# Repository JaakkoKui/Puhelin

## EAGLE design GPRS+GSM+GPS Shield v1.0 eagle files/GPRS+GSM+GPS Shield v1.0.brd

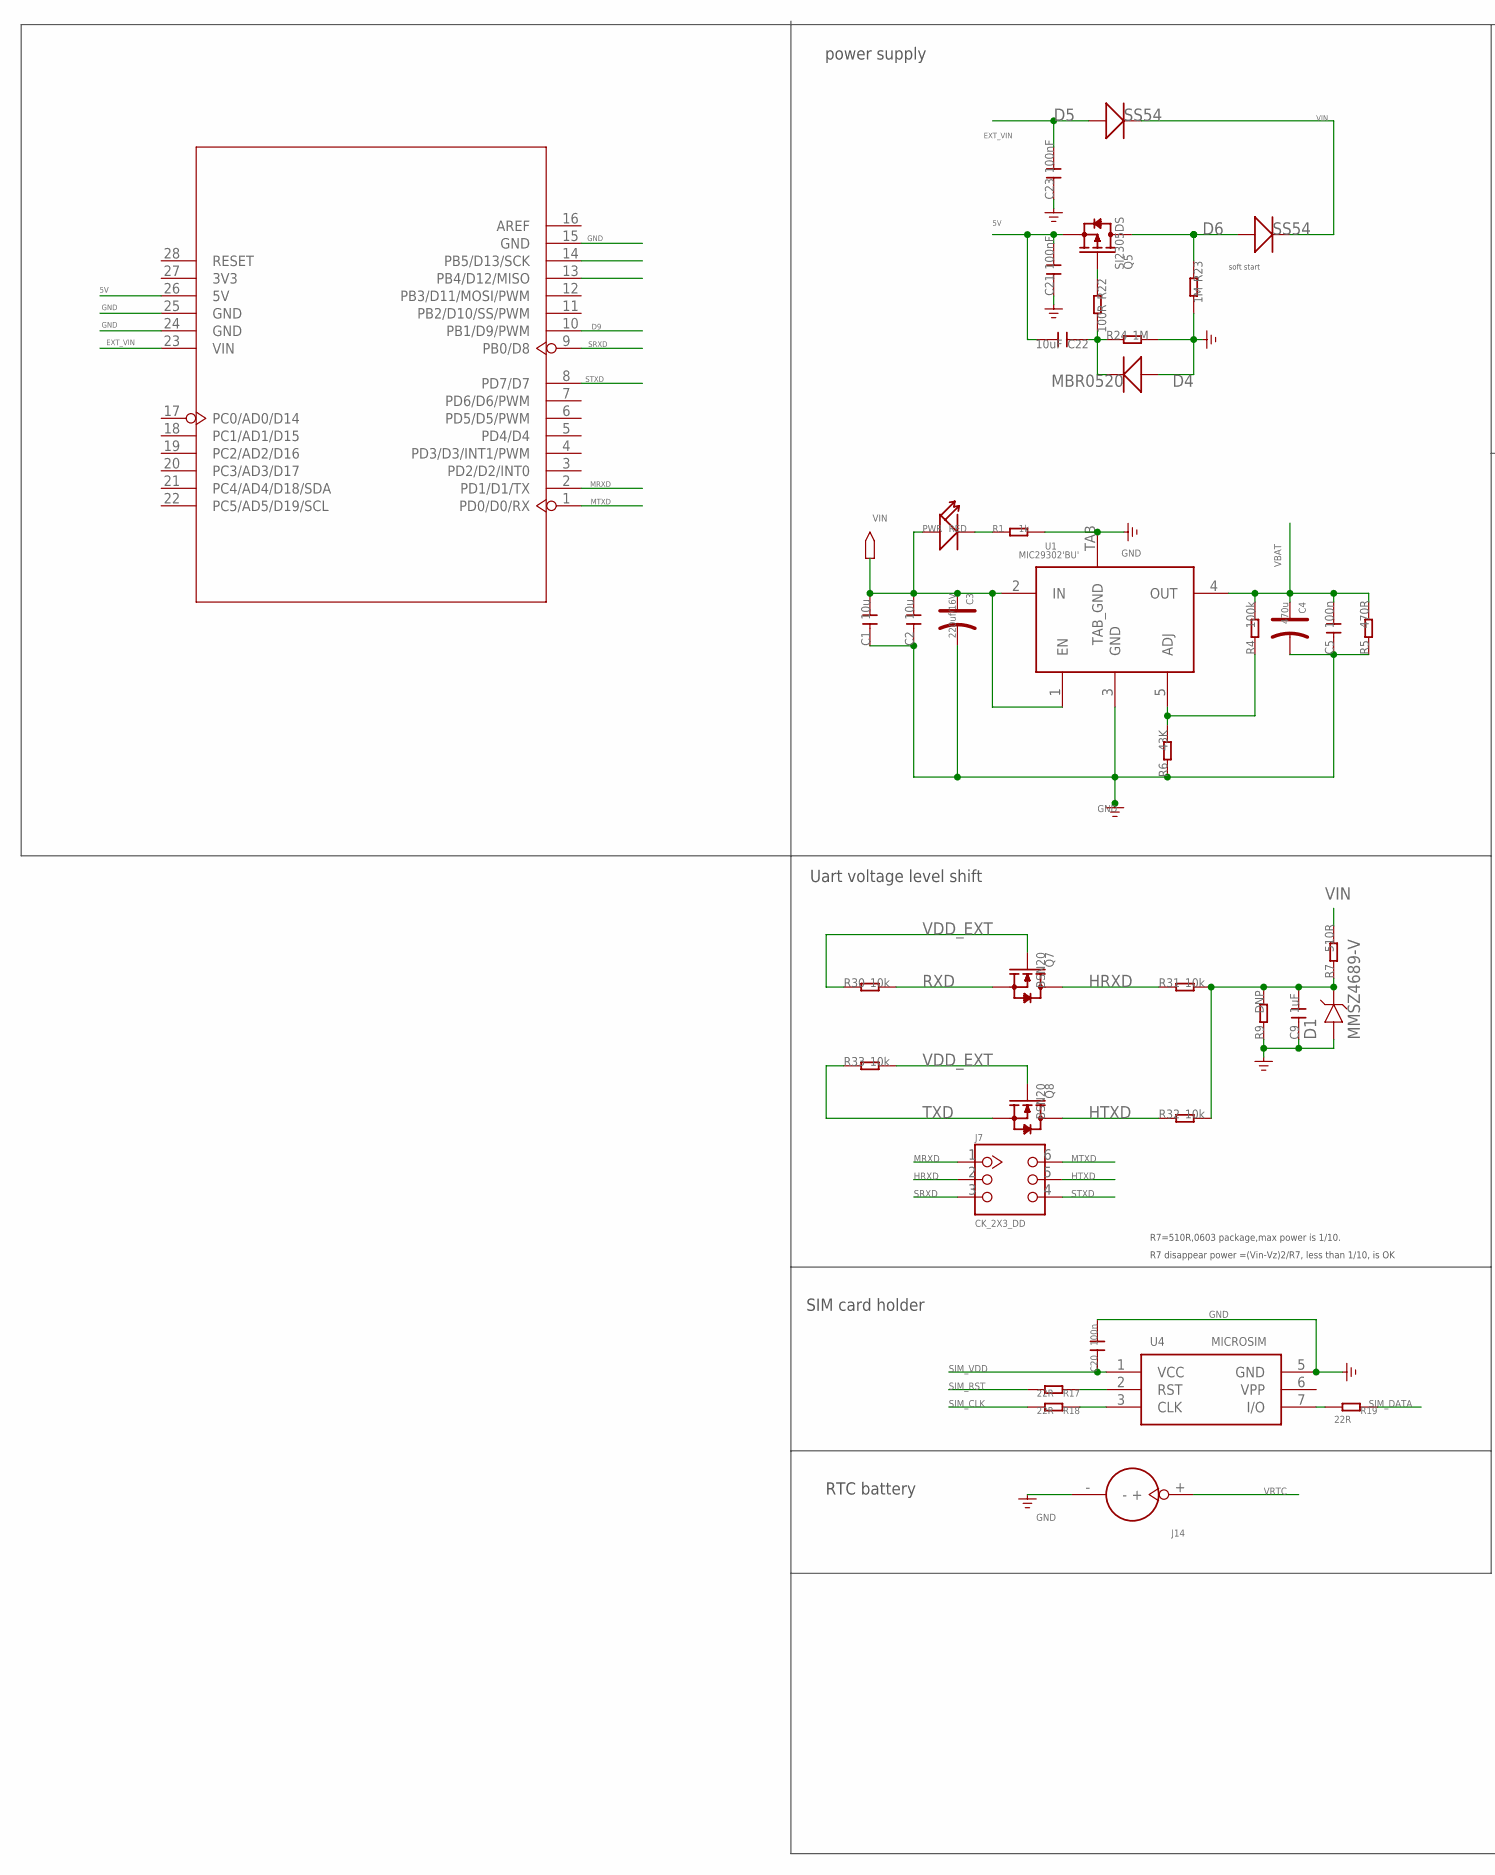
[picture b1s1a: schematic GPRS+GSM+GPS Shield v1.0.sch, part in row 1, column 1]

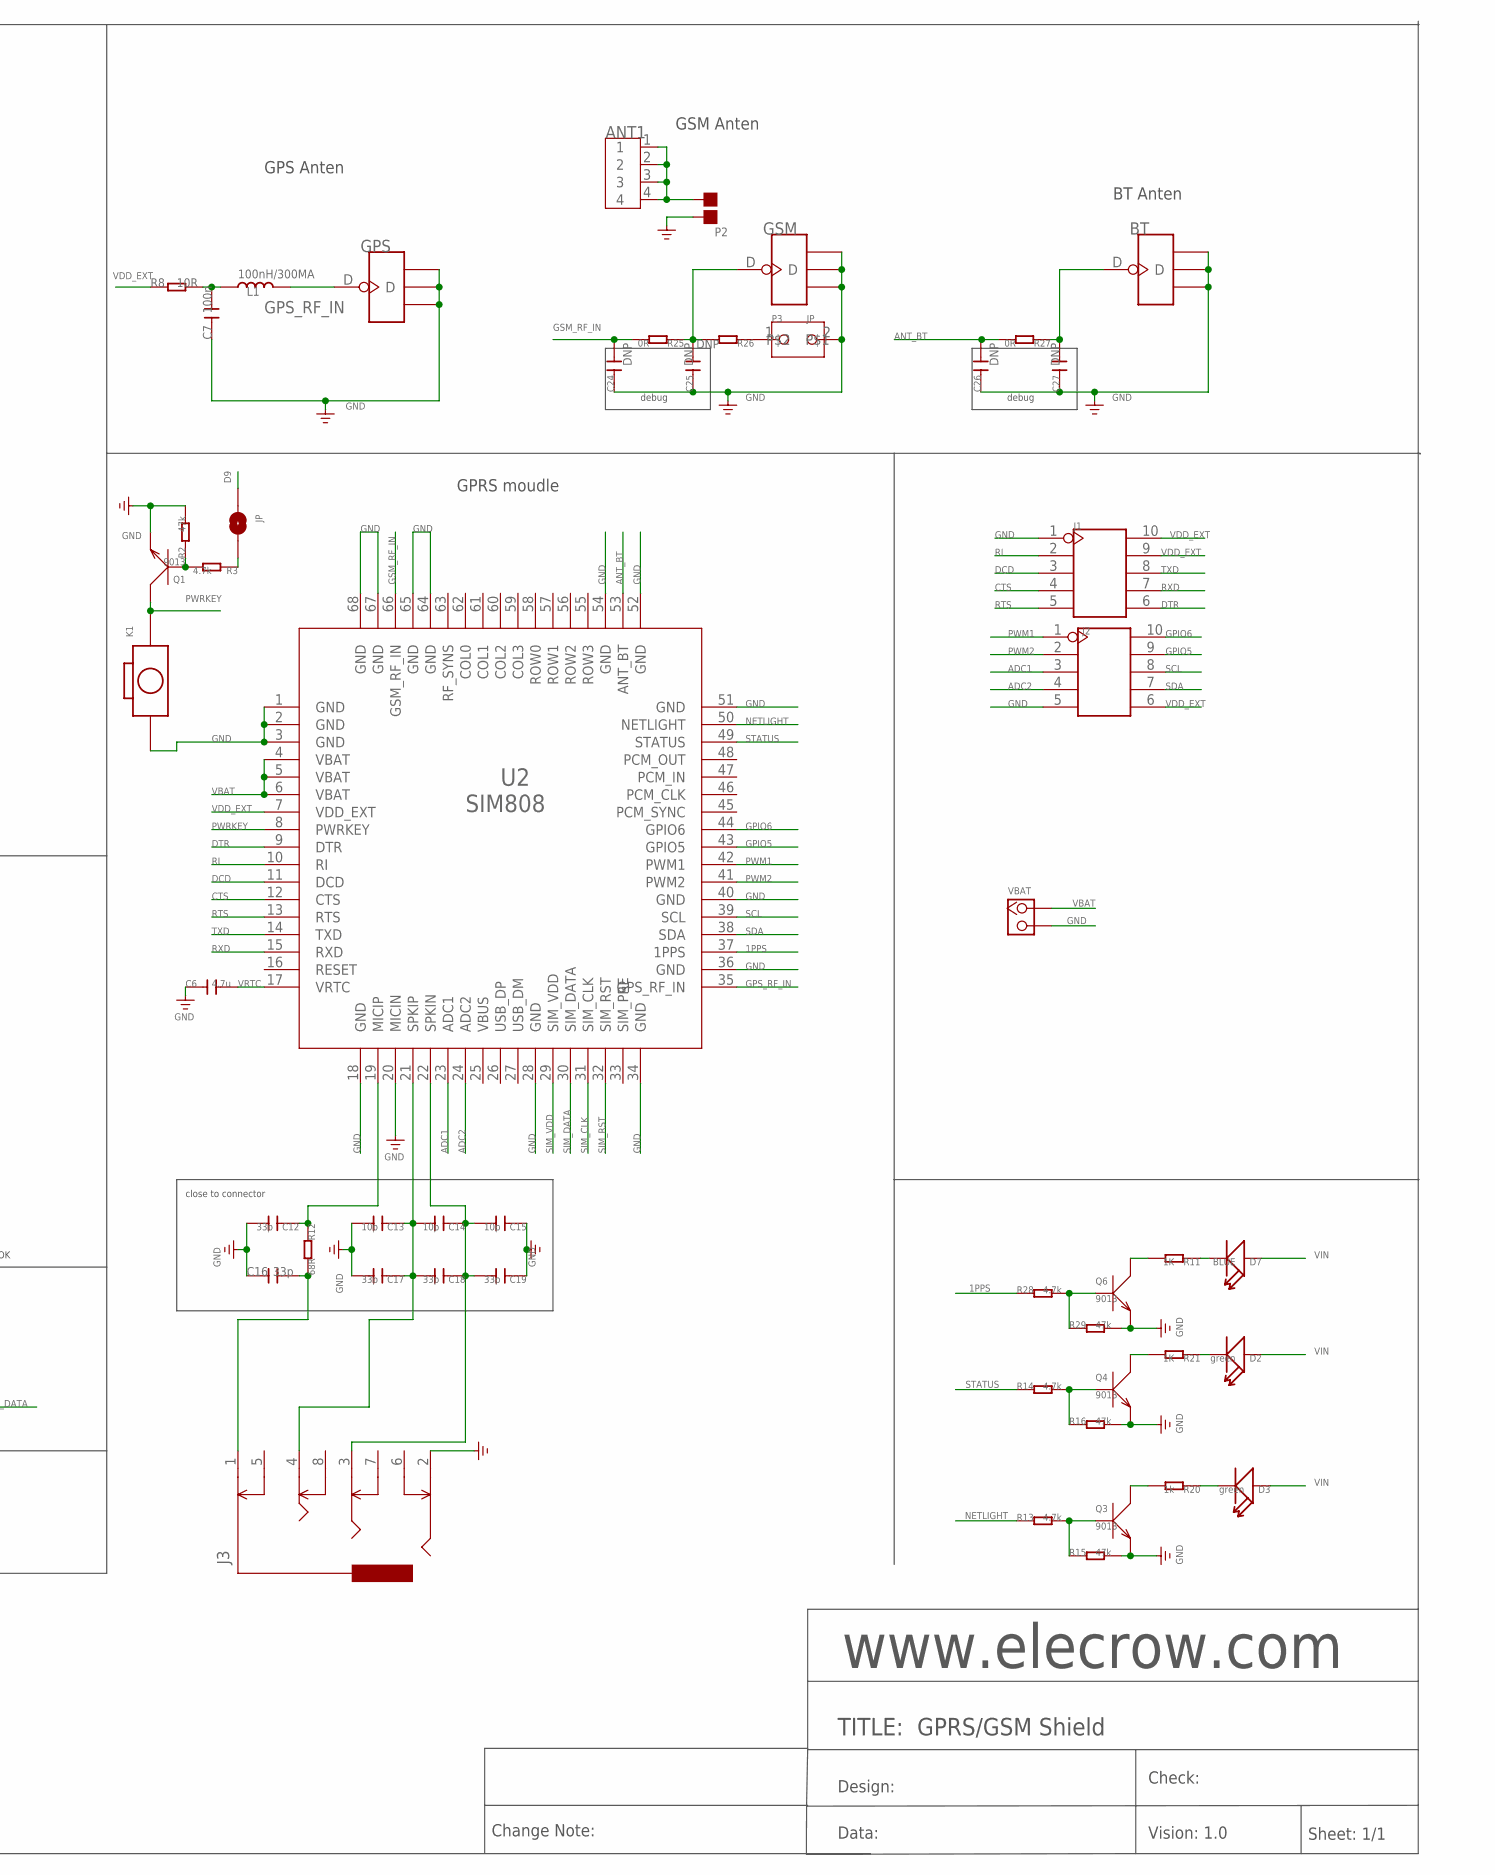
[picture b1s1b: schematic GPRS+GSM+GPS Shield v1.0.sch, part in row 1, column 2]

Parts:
ANT1: ANTENNA-SMA-IPX; SMA-TO-IPX
BT: ANTENNA-U-FL; 4P-U-FL
C1, C2: 10u; C0603
C3: 220uf/16V; AVX_D
C4: 470u; AVX_D
C5, C7, C20: 100n; C0603
C6: 4.7u; C0805
C9: 1uF; C0603
C12, C16: 33p; C0603
C13, C14, C15: 10p; C0402
C17, C18, C19: 33p; C0402
C21, C23: 100nF; C0603
C22: 10uF; C0805
C24, C25, C26, C27: DNP; C0402
D1: MMSZ4689-V; SOD123-2.7X1.6
D2, D3: green; LED-0603
D4: MBR0520; SOD123-2.7X1.6
D5, D6: SS54; SMB
D7: BLUE; LED-0603
GPS: ANTENNA-U-FL; 4P-U-FL
GSM: ANTENNA-U-FL; 4P-U-FL
J1, J2: HEADER-2X5P-2.54; 2X5P-2.54
J3: AUDIO-8P'PJ-3536-L6S'; 8P-3.5-SMD
J7: CK_2X3_DD; CK_2X3
J14: HOLDER-BATTERY-2P-CR1220; CR1220
JP: 0R/0805; 2P-SMD-3.3X2
K1: BOTTON_1_DP; BTN_5.0_RST
L1: 100nH/300MA; L0603
P2: PAD-JUMPER-2P; 2P-SMD-1.78X1.27
P3: JP
PWR: RED; D0603
Q1, Q3, Q4, Q6: 9013; SOT23
Q5: SI2305DS; SOT23
Q7, Q8: BSN20; SOT23
R1, R20: 1k; R0603
R2, R15, R16, R29: 47k; R0603
R3, R13, R14, R28: 4.7k; R0603
R4: 100k; R0603
R5: 470R; R0603
R6: 43K; R0603
R7: 510R; R0603
R8: 10R; R0603
R9: DNP; R0603
R11, R21: 1K; R0603
R12: 68R; R0603
R17, R18, R19: 22R; R0603
R22: 100R; R0603
R23, R24: 1M; R0603
R25, R27: 0R; R0402
R26: DNP; R0402
R30, R31, R32, R33: 10k; R0603
U1: MIC29302'BU'; TO-263
U2: SIM808
U3: UNO-SHILED; SHILED
U4: MICROSIM
VBAT: DNP; CK_1*2

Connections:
1PPS: R28.1, U2.37 (1PPS)
5V: C21.2, C22.2, Q5.2 (S), U3.26 (5V)
ADC1: J2.3, U2.23 (ADC1)
ADC2: J2.4, U2.24 (ADC2)
ANT_BT: C26.2, R27.2, U2.53 (ANT_BT)
COL0: U2.62 (COL0)
COL1: U2.61 (COL1)
COL2: U2.60 (COL2)
COL3: U2.59 (COL3)
CTS: J1.4, U2.12 (CTS)
D9: JP.1, U3.10 (PB1/D9/PWM)
DCD: J1.3, U2.11 (DCD)
DTR: J1.6, U2.9 (DTR)
EXT_VIN: C23.2, D5.+, U3.23 (VIN)
GND: BT.GND1, BT.GND2, BT.GND3, C1.1, C2.1, C3.-, C4.-, C5.1, C6.1, C7.1, C9.1, C12.2, C13.2, C15.1, C16.1, C17.2, C19.1, C20.2, C21.1, C23.1, C24.1, C25.1, C26.1, C27.1, D1.1, D4.1 (+), GPS.GND1, GPS.GND2, GPS.GND3, GSM.GND1, GSM.GND2, GSM.GND3, J1.1, J2.5, J3.2, J14.-, K1.P$1 (1), P2.2, P3.2, Q1.2 (E), Q3.2 (E), Q4.2 (E), Q6.2 (E), R1.2, R2.2, R5.1, R6.1, R9.1, R15.2, R16.2, R23.2, R24.2, R29.2, U1.3 (GND), U1.TAB (TAB_GND), U2.1 (GND), U2.2 (GND), U2.3 (GND), U2.18 (GND), U2.20 (MICIN), U2.28 (GND), U2.34 (GND), U2.36 (GND), U2.40 (GND), U2.51 (GND), U2.52 (GND), U2.54 (GND), U2.64 (GND), U2.65 (GND), U2.67 (GND), U2.68 (GND), U3.15 (GND), U3.24 (GND), U3.25 (GND), U4.5 (GND), VBAT.2
GPIO5: J2.9, U2.43 (GPIO5)
GPIO6: J2.10, U2.44 (GPIO6)
GPS_RF_IN: GPS.D, L1.2, U2.35 (GPS_RF_IN)
GSM_RF_IN: C24.2, R25.2, U2.66 (GSM_RF_IN)
HRXD: J7.2, Q7.3 (D), R31.1
HTXD: J7.5, Q8.3 (D), R32.1
MRXD: J7.1, U3.2 (PD1/D1/TX)
MTXD: J7.6, U3.1 (PD0/D0/RX)
unnamed: R19.2, U4.7 (I/O)
unnamed: R4.1, R6.2, U1.5 (ADJ)
unnamed: Q3.3 (C), R20.2
unnamed: Q6.3 (C), R11.2
unnamed: R18.1, U4.3 (CLK)
unnamed: R17.1, U4.2 (RST)
unnamed: D3.-, R20.1
unnamed: Q3.1 (B), R13.2, R15.1
unnamed: C9.2, D1.2, R7.1, R9.2, R31.2, R32.2
unnamed: Q5.1 (G), R22.1
unnamed: ANT1.1, ANT1.2, ANT1.3, ANT1.4, P2.1
unnamed: C12.1, R12.1, U2.19 (MICIP)
unnamed: JP.2, R3.1
unnamed: C13.1, C14.2, C17.1, C18.2, J3.4, U2.21 (SPKIP)
unnamed: Q4.3 (C), R21.2
unnamed: D2.-, R21.1
unnamed: Q4.1 (B), R14.2, R16.1
unnamed: C14.1, C15.2, C18.1, C19.2, J3.3, U2.22 (SPKIN)
unnamed: D6.+, Q5.3 (D), R23.1
unnamed: C7.2, L1.1, R8.2
unnamed: D7.-, R11.1
unnamed: Q6.1 (B), R28.2, R29.1
unnamed: C25.2, GSM.D, R25.1, R26.2
unnamed: P3.1, R26.1
unnamed: BT.D, C27.2, R27.1
unnamed: C16.2, J3.1, R12.2
unnamed: Q1.1 (B), R2.1, R3.2
unnamed: C22.1, D4.2 (-), R22.2, R24.1
unnamed: PWR.-, R1.1
NETLIGHT: R13.1, U2.50 (NETLIGHT)
PWM1: J2.1, U2.42 (PWM1)
PWM2: J2.2, U2.41 (PWM2)
PWRKEY: K1.P$2 (2), Q1.3 (C), U2.8 (PWRKEY)
RF_SYNS: U2.63 (RF_SYNS)
RI: J1.2, U2.10 (RI)
ROW0: U2.58 (ROW0)
ROW1: U2.57 (ROW1)
ROW2: U2.56 (ROW2)
ROW3: U2.55 (ROW3)
RTS: J1.5, U2.13 (RTS)
RXD: J1.7, Q7.2 (S), R30.2, U2.15 (RXD)
SCL: J2.8, U2.39 (SCL)
SDA: J2.7, U2.38 (SDA)
SIM_CLK: R18.2, U2.31 (SIM_CLK)
SIM_DATA: R19.1, U2.30 (SIM_DATA)
SIM_RST: R17.2, U2.32 (SIM_RST)
SIM_VDD: C20.1, U2.29 (SIM_VDD), U4.1 (VCC)
SRXD: J7.3, U3.9 (PB0/D8)
STATUS: R14.1, U2.49 (STATUS)
STXD: J7.4, U3.8 (PD7/D7)
TXD: J1.8, Q8.2 (S), R33.1, U2.14 (TXD)
VBAT: C4.+, C5.2, R4.2, R5.2, U1.4 (OUT), U2.4 (VBAT), U2.5 (VBAT), U2.6 (VBAT), VBAT.1
VDD_EXT: J1.9, J1.10, J2.6, Q7.1 (G), Q8.1 (G), R8.1, R30.1, R33.2, U2.7 (VDD_EXT)
VIN: C1.2, C2.2, C3.+, D2.+, D3.+, D5.-, D6.-, D7.+, PWR.+, R7.2, U1.1 (EN), U1.2 (IN)
VRTC: C6.2, J14.+, U2.17 (VRTC)

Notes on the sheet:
close to connector
TITLE: GPRS/GSM Shield
www.elecrow.com
Design:
Check:
Data:
Vision: 1.0
Sheet: 1/1
power supply
Uart voltage level shift
R7=510R,0603 package,max power is 1/10.
R7 disappear power =(Vin-Vz)2/R7, less than 1/10, is OK
RTC battery
SIM card holder
GPRS moudle
Change Note:
soft start
debug
GPS Anten
GSM Anten
BT Anten

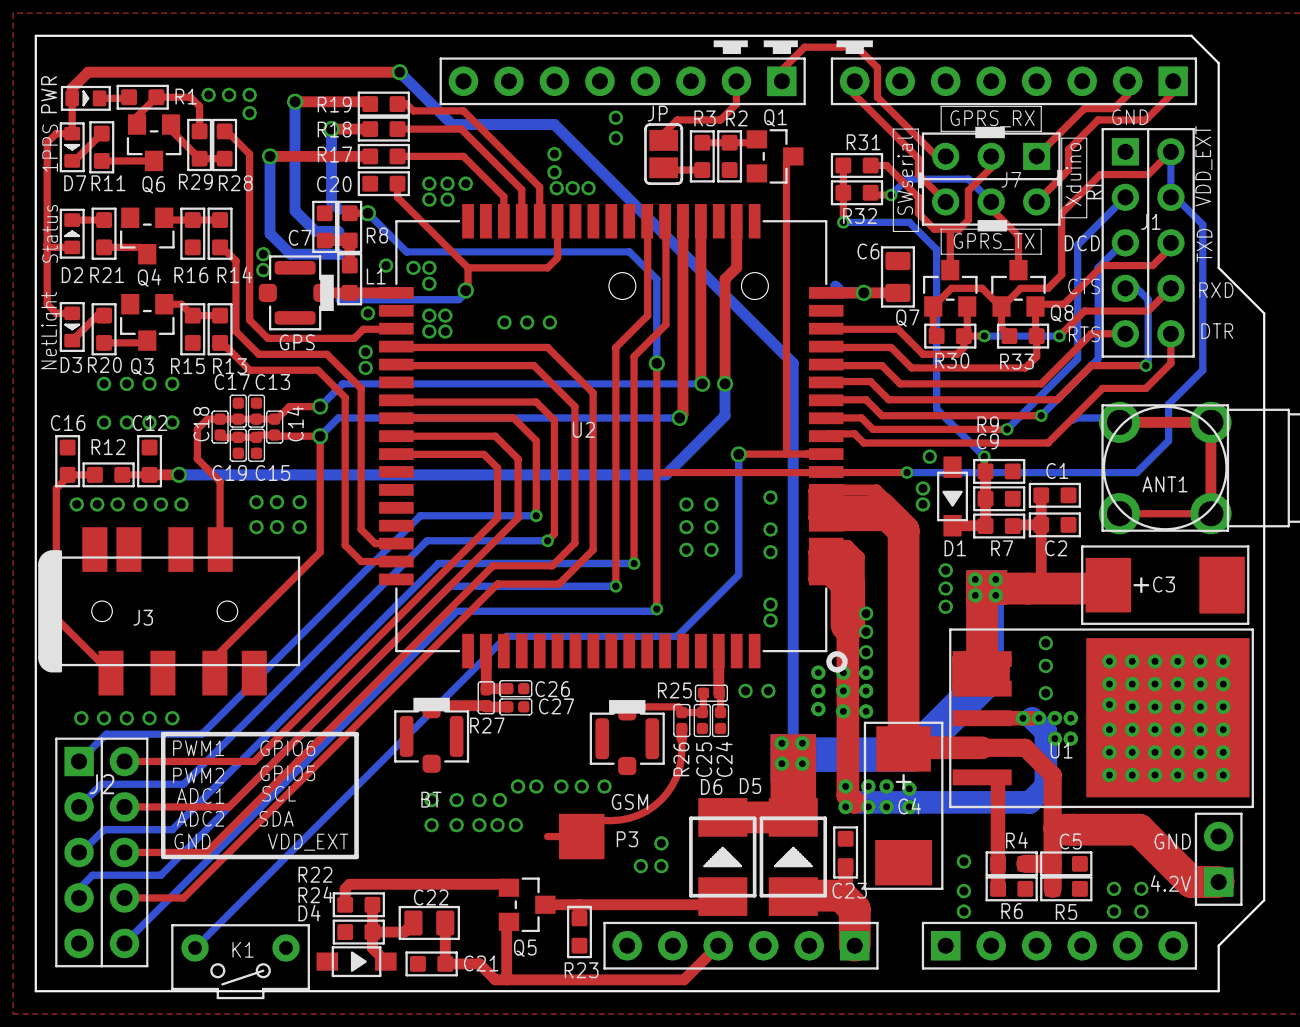
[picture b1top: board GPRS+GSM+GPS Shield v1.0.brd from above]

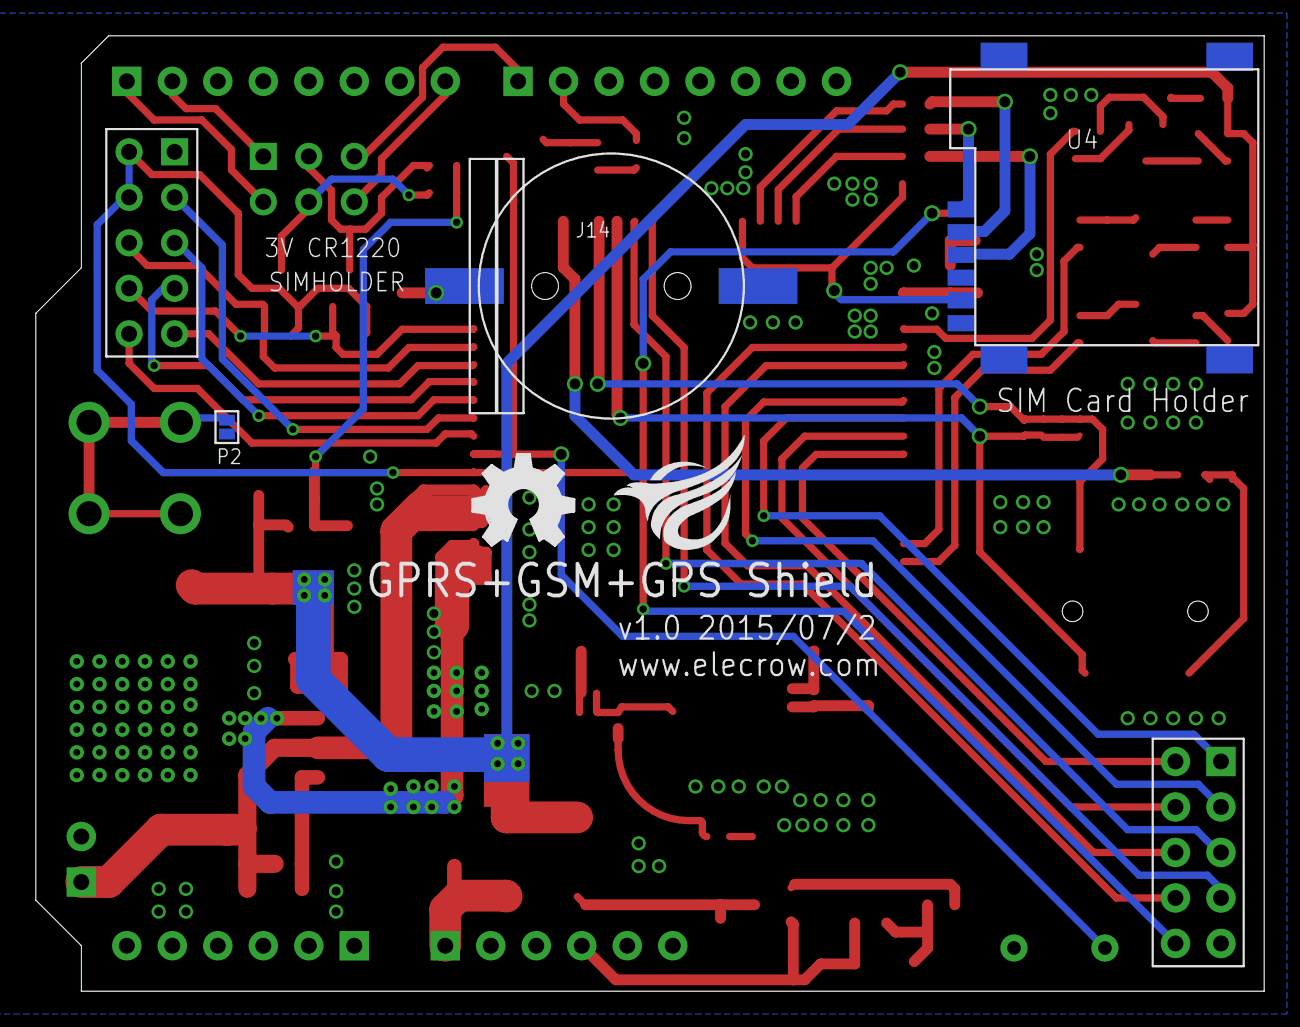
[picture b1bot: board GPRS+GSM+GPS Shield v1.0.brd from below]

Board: 2 copper layers, 68.6 x 53.3 mm, 92 parts (5 on the bottom side), 69 nets.

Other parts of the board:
LOGO2: LOGO-OSHW-FILLX0200-NT; OSHW_FILLX200_NOTEXT
U$4: ELECROW_NRW_6

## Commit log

2020-01-15 laitteisto käynnissä
2020-01-16 Pohja
2020-01-21 Pohjav2, ei toimi, muutoksia tulossa
2020-01-21 Toimii, saldo loppu
2020-01-28 Sotkettud
2020-01-28 Korjattud
2020-01-28 Siistittyd
2020-01-29 Melkein valmis
2020-01-29 Done
2020-01-30 Korjattud v.2
2020-01-30 Dokumentti
2020-01-30 Dokumentointi2
2020-01-30 Dokumentointi3
2020-01-30 Dokumentointi8
